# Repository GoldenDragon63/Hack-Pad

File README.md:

# hackpad

* Keyboard Maintainer: [Goldendragon63]
* Hardware Supported: The PCBs, controllers supported
* Hardware Availability:Links to where you can find this hardware

Make example for this keyboard (after setting up your build environment):

    make planck/rev4:default

Flashing example for this keyboard:

    make planck/rev4:default:flash

See the [build environment setup](getting_started_build_tools) and the [make instructions](getting_started_make_guide) for more information. Brand new to QMK? Start with our [Complete Newbs Guide](newbs).

## Bootloader

Enter the bootloader in 3 ways:

* **Bootmagic reset**: Hold down the key at (0,0) in the matrix (usually the top left key or Escape) and plug in the keyboard
* **Physical reset button**: Briefly press the button on the back of the PCB - some may have pads you must short instead
* **Keycode in layout**: Press the key mapped to `QK_BOOT` if it is available

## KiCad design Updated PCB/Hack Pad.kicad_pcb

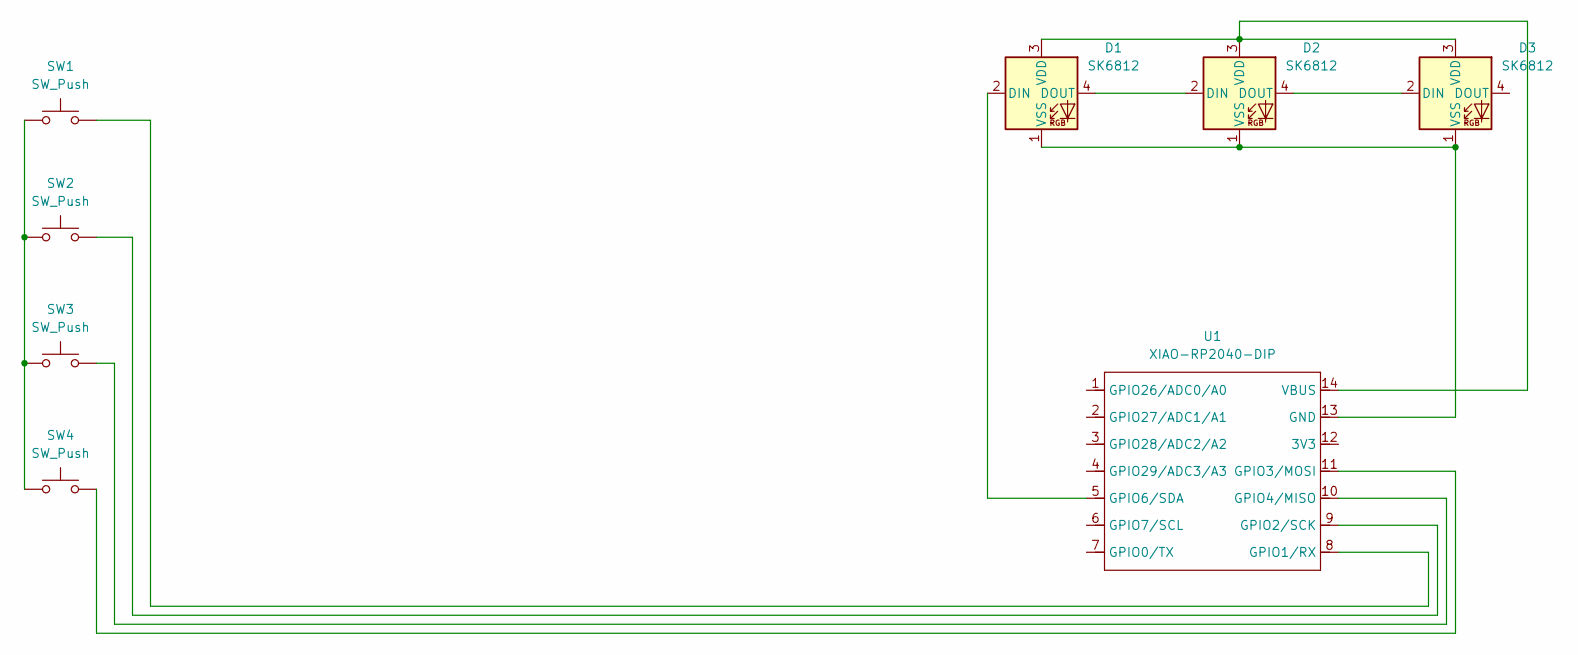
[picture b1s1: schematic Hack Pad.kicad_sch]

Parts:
D1, D2, D3: SK6812; LED_SK6812MINI_PLCC4_3.5x3.5mm_P1.75mm
SW1, SW2, SW3, SW4: SW_Push; SW_Cherry_MX_1.00u_PCB
U1: XIAO-RP2040-DIP

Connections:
unnamed: D1.2 (DIN), U1.5 (GPIO6/SDA)
unnamed: D1.4 (DOUT), D2.2 (DIN)
unnamed: D1.3 (VDD), D2.3 (VDD), D3.3 (VDD), U1.14 (VBUS)
unnamed: D1.1 (VSS), D2.1 (VSS), D3.1 (VSS), U1.13 (GND)
unnamed: D2.4 (DOUT), D3.2 (DIN)
unnamed: SW1.1, SW2.1, SW3.1, SW4.1
unnamed: SW1.2, U1.8 (GPIO1/RX)
unnamed: SW2.2, U1.9 (GPIO2/SCK)
unnamed: SW4.2, U1.11 (GPIO3/MOSI)
unnamed: SW3.2, U1.10 (GPIO4/MISO)

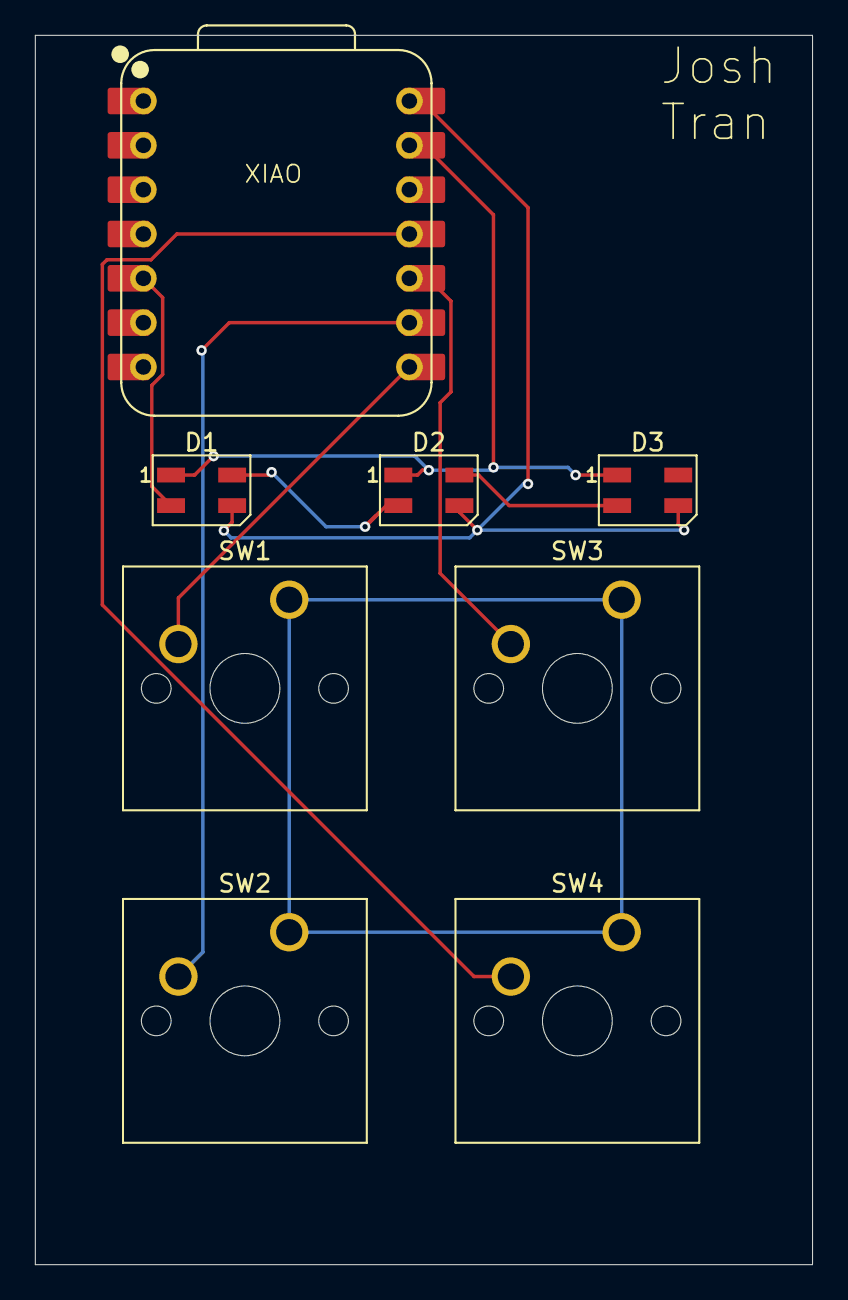
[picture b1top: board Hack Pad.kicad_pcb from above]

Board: 2 copper layers, 44.5 x 70.4 mm, 8 parts (0 on the bottom side), 10 nets.

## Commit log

2025-06-01 Uploaded CAD
2025-06-01 For PCB board
2025-06-17 QMK files uploaded
2025-06-17 Here is the updated PCB Files
    (I'm not sure how to delete the old ones)
